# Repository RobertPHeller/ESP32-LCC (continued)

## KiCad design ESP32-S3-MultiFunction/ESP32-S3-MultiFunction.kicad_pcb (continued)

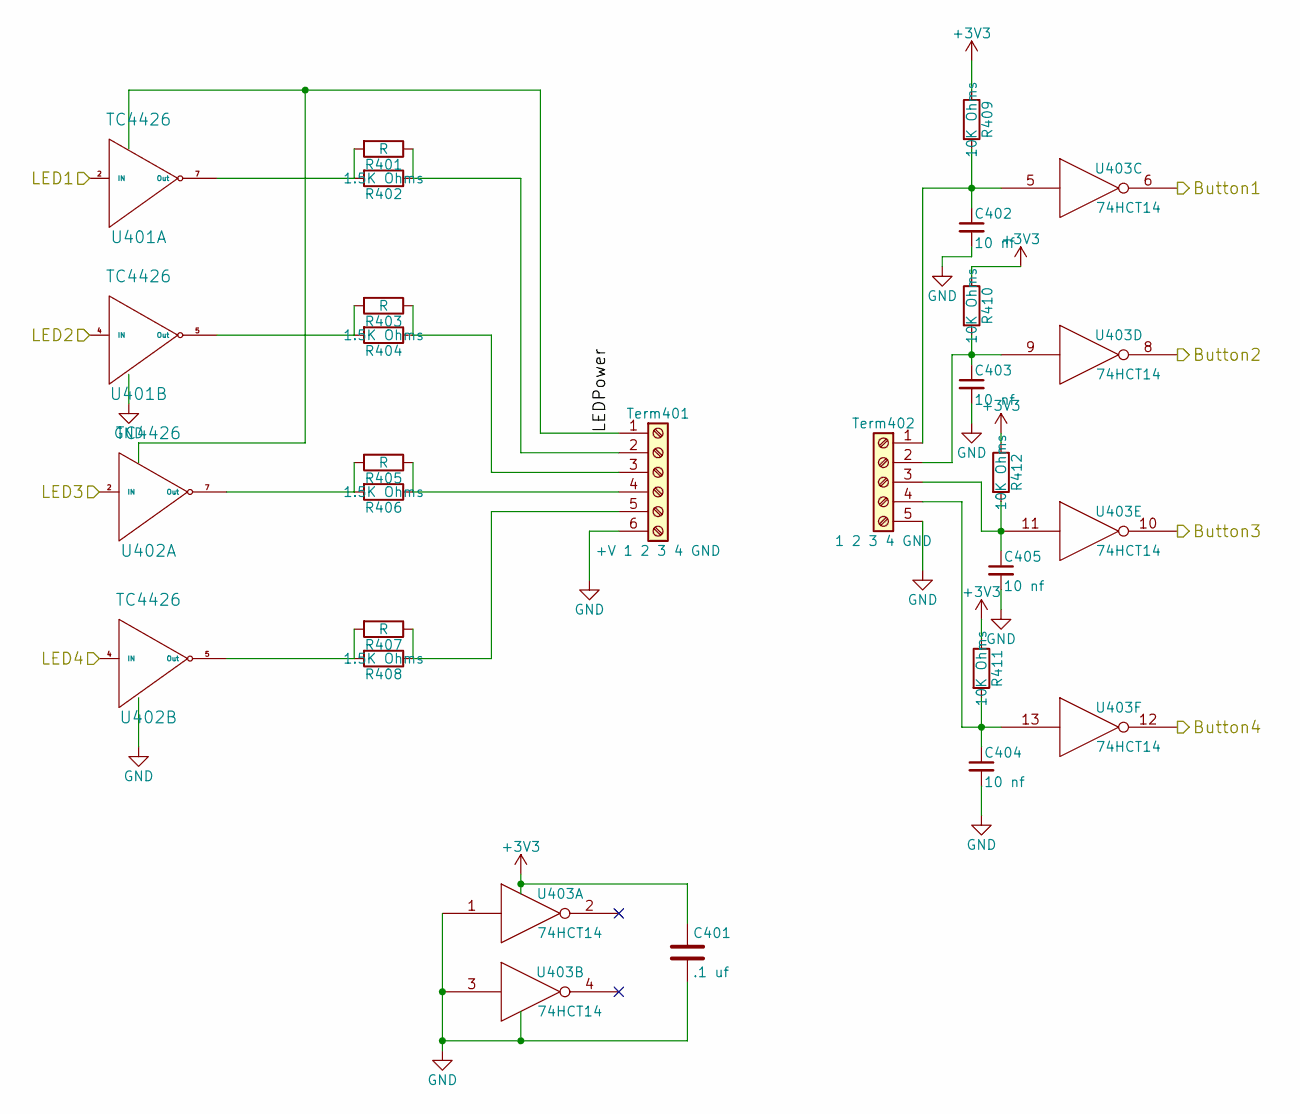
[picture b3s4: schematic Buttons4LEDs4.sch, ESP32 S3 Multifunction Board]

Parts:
C401: .1 uf; C_0603; Mouser Part Number 710-885012206095
C402, C403, C404, C405: 10 nf; C_0603; Mouser Part Number 710-885382206002
R401, R403, R405, R407: R; R_Axial_DIN0207_L6.3mm_D2.5mm_P7.62mm_Horizontal
R402, R404, R406, R408: 1.5K Ohms; R_0603; Mouser Part Number 71-CRCW06031K50JNEAC
R409, R410, R411, R412: 10K Ohms; R_0603; Mouser Part Number 71-CRCW060310K0JNEBC
Term401: +V 1 2 3 4 GND; TerminalBlock_Pheonix_MPT-2.54mm_6pol; Mouser Part Number 651-1725698
Term402: 1 2 3 4 GND; TerminalBlock_Pheonix_MPT-2.54mm_5pol; Mouser Part Number 651-1725685
U401, U402: TC4426; SOIC-8_3.9x4.9mm_Pitch1.27mm; Mouser Part Number 579-TC1426COA713
U403: 74HCT14; SOIC-14_3.9x8.7mm_Pitch1.27mm; Mouser Part Number 595-CD74HC14M

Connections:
/Buttons and LEDs/Button1: U403.6; also elsewhere on the board
/Buttons and LEDs/Button2: U403.8; also elsewhere on the board
/Buttons and LEDs/Button3: U403.10; also elsewhere on the board
/Buttons and LEDs/Button4: U403.12; also elsewhere on the board
/ESP32 MCU/GPIO1(LEDS4): U402.4 (IN); also elsewhere on the board
/ESP32 MCU/GPIO17(LEDS1): U401.2 (IN); also elsewhere on the board
/ESP32 MCU/GPIO18(LEDS2): U401.4 (IN); also elsewhere on the board
/ESP32 MCU/GPIO21(LEDS3): U402.2 (IN); also elsewhere on the board
GND: C401.2, C402.2, C403.2, C404.2, C405.2, Term401.6, Term402.5, U401.3 (GND), U402.3 (GND), U403.1, U403.3, U403.7 (GND); also elsewhere on the board
unnamed: C402.1, R409.2, Term402.1, U403.5
unnamed: C403.1, R410.2, Term402.2, U403.9
unnamed: C404.1, R411.2, Term402.4, U403.13
unnamed: C405.1, R412.2, Term402.3, U403.11
unnamed: R401.1, R402.1, Term401.2
unnamed: R401.2, R402.2, U401.7 (Out)
unnamed: R403.1, R404.1, Term401.3
unnamed: R403.2, R404.2, U401.5 (Out)
unnamed: R405.1, R406.1, Term401.4
unnamed: R405.2, R406.2, U402.7 (Out)
unnamed: R407.1, R408.1, Term401.5
unnamed: R407.2, R408.2, U402.5 (Out)
VPower: Term401.1, U401.6 (VPower), U402.6 (VPower)

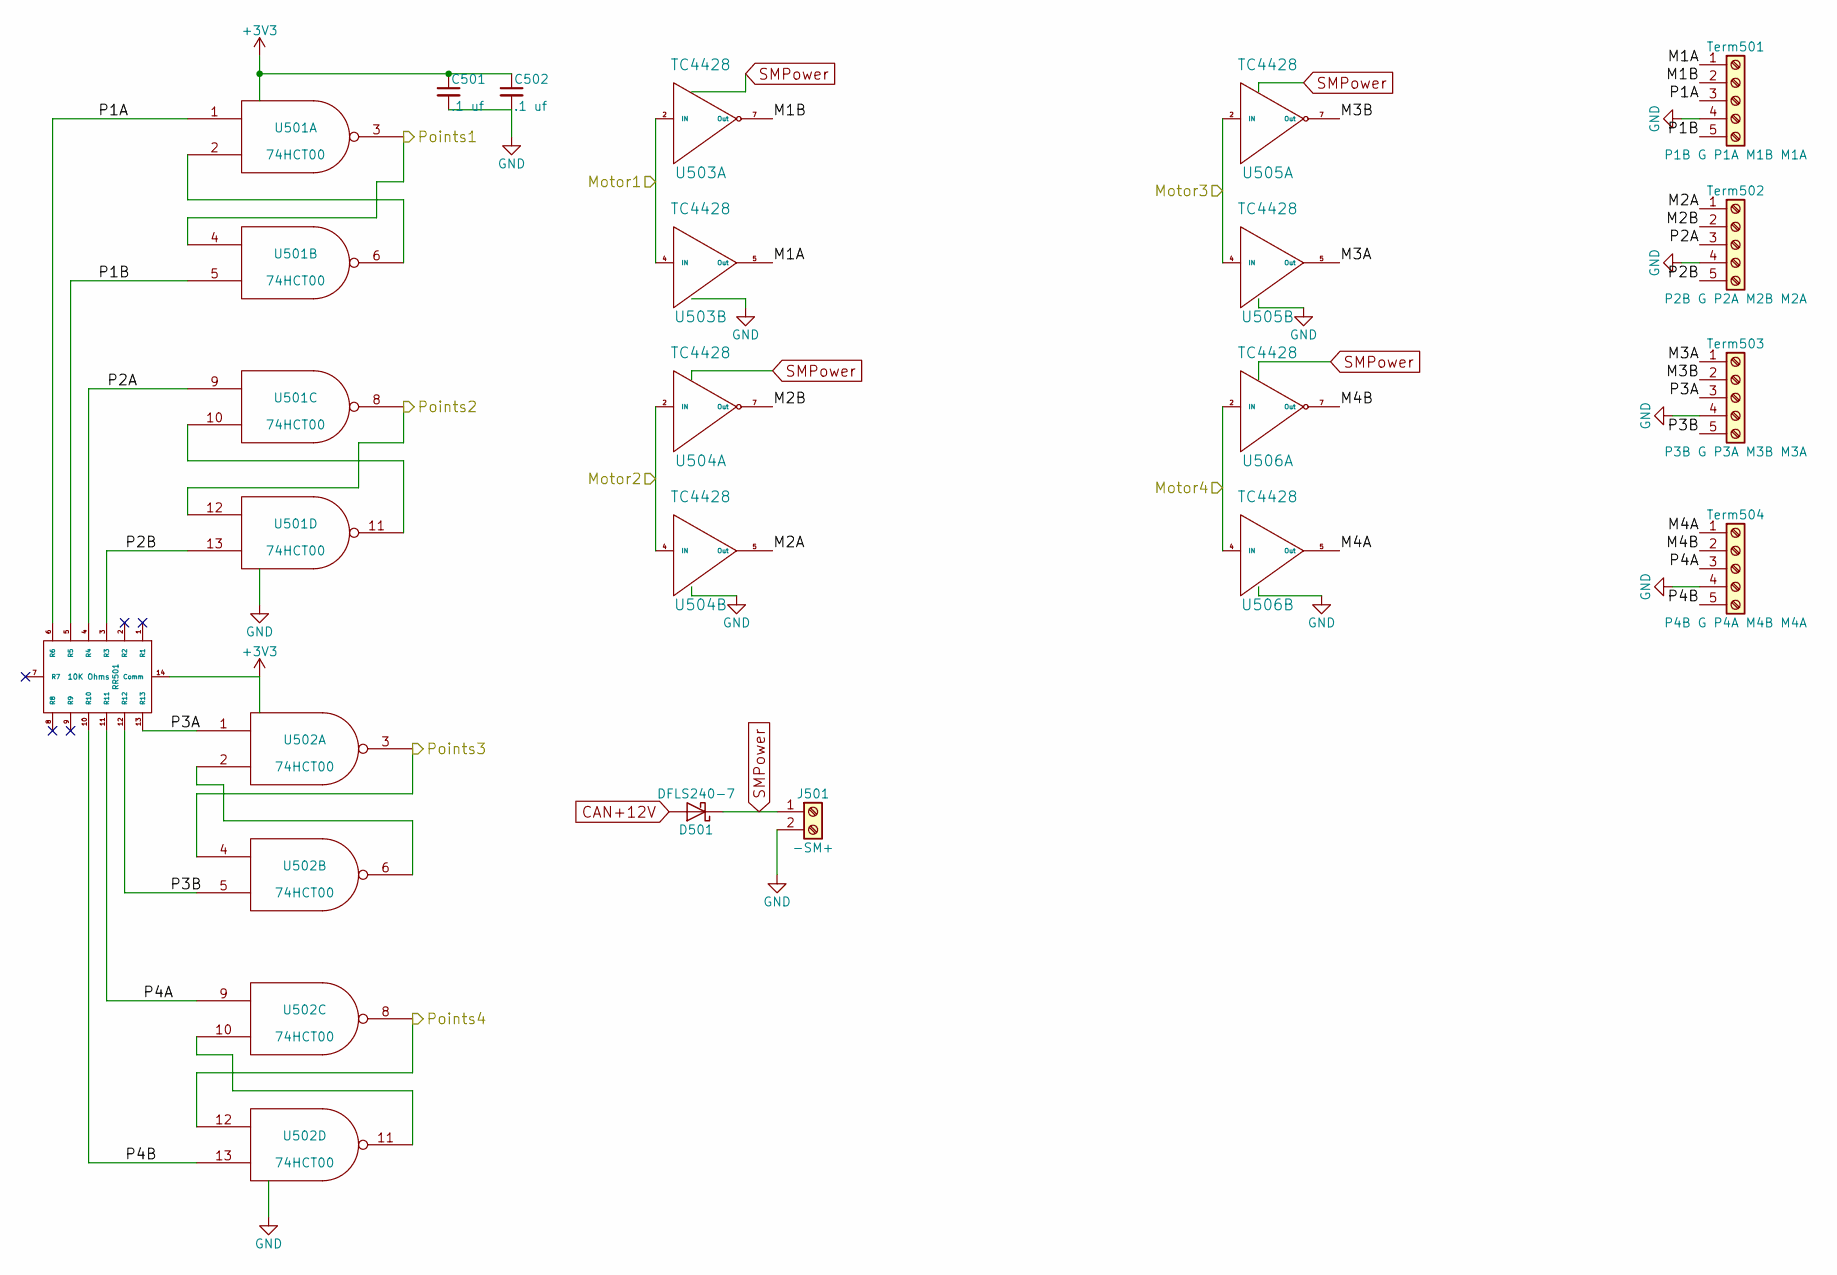
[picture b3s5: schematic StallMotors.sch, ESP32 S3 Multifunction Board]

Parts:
C501, C502: .1 uf; C_0603; Mouser Part Number 710-885012206095
D501: DFLS240-7; D_PowerDI-123; Mouser Part Number 621-DFLS240-7
J501: -SM+; TerminalBlock_Pheonix_MPT-2.54mm_2pol; Mouser Part Number 651-172565
RR501: 10K Ohms; 4814P; Mouser Part Number 652-4814P-2LF-10K
Term501: P1B G P1A M1B M1A; TerminalBlock_Pheonix_MPT-2.54mm_5pol; Mouser Part Number 651-1725685
Term502: P2B G P2A M2B M2A; TerminalBlock_Pheonix_MPT-2.54mm_5pol; Mouser Part Number 651-1725685
Term503: P3B G P3A M3B M3A; TerminalBlock_Pheonix_MPT-2.54mm_5pol; Mouser Part Number 651-1725685
Term504: P4B G P4A M4B M4A; TerminalBlock_Pheonix_MPT-2.54mm_5pol; Mouser Part Number 651-1725685
U501, U502: 74HCT00; SOIC-14_3.9x8.7mm_Pitch1.27mm; Mouser Part Number 595-SN74AHC00D
U503, U504, U505, U506: TC4428; SOIC-8_3.9x4.9mm_Pitch1.27mm; Mouser Part Number 579-TC4428VOA

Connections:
/ESP32 MCU/GPIO8(Motor3): U505.2 (IN), U505.4 (IN); also elsewhere on the board
/ESP32 MCU/GPIO9(Motor1): U503.2 (IN), U503.4 (IN); also elsewhere on the board
/ESP32 MCU/GPIO10(Points4): U502.8, U502.12; also elsewhere on the board
/ESP32 MCU/GPIO11(Motor2): U504.2 (IN), U504.4 (IN); also elsewhere on the board
/ESP32 MCU/GPIO12(Points1): U501.3, U501.4; also elsewhere on the board
/ESP32 MCU/GPIO13(Points2): U501.8, U501.12; also elsewhere on the board
/ESP32 MCU/GPIO14(Points3): U502.3, U502.4; also elsewhere on the board
/ESP32 MCU/GPIO33(Motor4): U506.2 (IN), U506.4 (IN); also elsewhere on the board
/Stall Motors/M1A: Term501.1, U503.5 (Out)
/Stall Motors/M1B: Term501.2, U503.7 (Out)
/Stall Motors/M2A: Term502.1, U504.5 (Out)
/Stall Motors/M2B: Term502.2, U504.7 (Out)
/Stall Motors/M3A: Term503.1, U505.5 (Out)
/Stall Motors/M3B: Term503.2, U505.7 (Out)
/Stall Motors/M4A: Term504.1, U506.5 (Out)
/Stall Motors/M4B: Term504.2, U506.7 (Out)
/Stall Motors/P1A: RR501.6 (R6), Term501.3, U501.1
/Stall Motors/P1B: RR501.5 (R5), Term501.5, U501.5
/Stall Motors/P2A: RR501.4 (R4), Term502.3, U501.9
/Stall Motors/P2B: RR501.3 (R3), Term502.5, U501.13
/Stall Motors/P3A: RR501.13 (R13), Term503.3, U502.1
/Stall Motors/P3B: RR501.12 (R12), Term503.5, U502.5
/Stall Motors/P4A: RR501.11 (R11), Term504.3, U502.9
/Stall Motors/P4B: RR501.10 (R10), Term504.5, U502.13
CAN +12V: D501.2 (A); also elsewhere on the board
GND: C501.2, C502.2, J501.2, Term501.4, Term502.4, Term503.4, Term504.4, U501.7 (GND), U502.7 (GND), U503.3 (GND), U504.3 (GND), U505.3 (GND), U506.3 (GND); also elsewhere on the board
unnamed: U501.2, U501.6
unnamed: U501.10, U501.11
unnamed: U502.2, U502.6
unnamed: U502.10, U502.11
SMPower: D501.1 (K), J501.1, U503.6 (Vdd), U504.6 (Vdd), U505.6 (Vdd), U506.6 (Vdd)

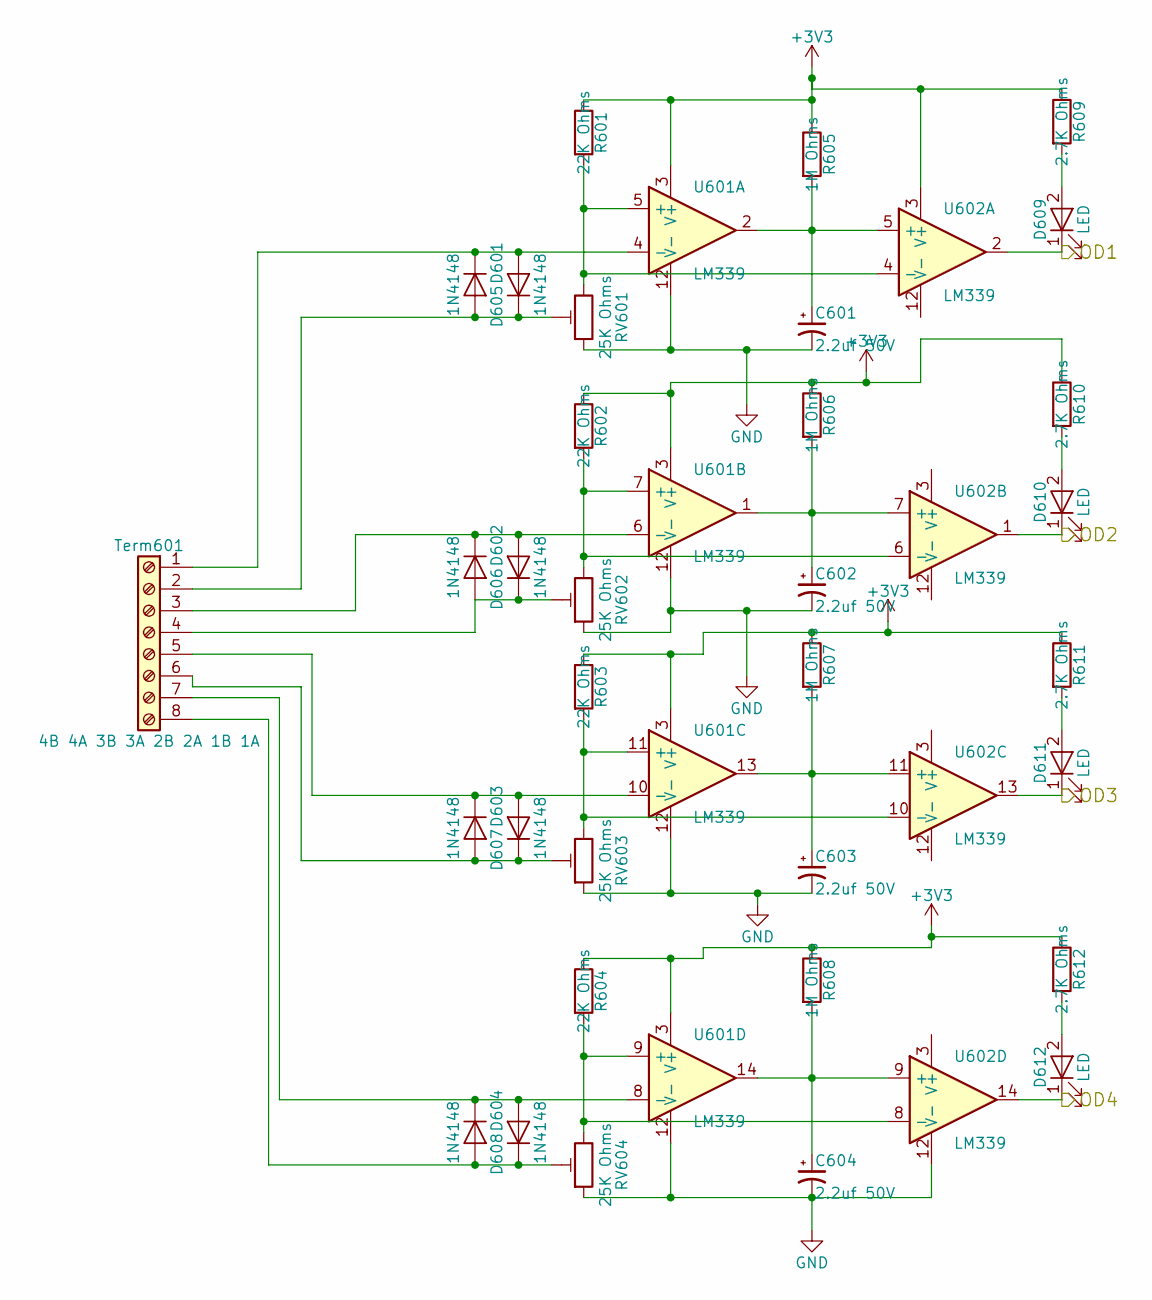
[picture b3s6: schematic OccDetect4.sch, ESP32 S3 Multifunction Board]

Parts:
C601, C602, C603, C604: 2.2uf 50V; CP_Elec_4x5.7; Mouser Part Number 710-865080140002
D601, D602, D603, D604, D605, D606, D607, D608: 1N4148; D_SOD-323; Mouser Part Number 750-1N4148WS-HF
D609, D610, D611, D612: LED; LED_0603; Mouser Part Number 710-150060SS55040
R601, R602, R603, R604: 22K Ohms; R_0603; Mouser Part Number 71-RCG060322K0JNEA
R605, R606, R607, R608: 1M Ohms; R_0603; Mouser Part Number 71-CRCW06031M00JNEAC
R609, R610, R611, R612: 2.7K Ohms; R_0603; Mouser Part Number 71-CRCW06032K70JNEAC
RV601, RV602, RV603, RV604: 25K Ohms; Potentiometer_Trimmer_Bourns_3214J; Mouser Part Number 652-3314J-1-253E
Term601: 4B 4A 3B 3A 2B 2A 1B 1A; TerminalBlock_Pheonix_MPT-2.54mm_8pol; Mouser Part Number 651-1725711
U601, U602: LM339; SOIC-14_3.9x8.7mm_Pitch1.27mm; Mouser Part Number 595-LM339DR

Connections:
/ESP32 MCU/GPIO7(OD4): D612.1 (K), U602.14; also elsewhere on the board
/ESP32 MCU/GPIO34(OD1): D609.1 (K), U602.2; also elsewhere on the board
/ESP32 MCU/GPIO35(OD2): D610.1 (K), U602.1; also elsewhere on the board
/ESP32 MCU/GPIO36(OD3): D611.1 (K), U602.13; also elsewhere on the board
GND: C601.2, C602.2, C603.2, C604.2, RV601.1, RV602.1, RV603.1, RV604.1, U601.12 (V-), U602.12 (V-); also elsewhere on the board
unnamed: C601.1, R605.2, U601.2, U602.5 (+)
unnamed: C602.1, R606.2, U601.1, U602.7 (+)
unnamed: C603.1, R607.2, U601.13, U602.11 (+)
unnamed: C604.1, R608.2, U601.14, U602.9 (+)
unnamed: D601.1 (K), D605.2 (A), Term601.1, U601.4 (-)
unnamed: D601.2 (A), D605.1 (K), RV601.2, Term601.2
unnamed: D602.1 (K), D606.2 (A), Term601.3, U601.6 (-)
unnamed: D602.2 (A), D606.1 (K), RV602.2, Term601.4
unnamed: D603.1 (K), D607.2 (A), Term601.5, U601.10 (-)
unnamed: D603.2 (A), D607.1 (K), RV603.2, Term601.6
unnamed: D604.1 (K), D608.2 (A), Term601.7, U601.8 (-)
unnamed: D604.2 (A), D608.1 (K), RV604.2, Term601.8
unnamed: D609.2 (A), R609.2
unnamed: D610.2 (A), R610.2
unnamed: D611.2 (A), R611.2
unnamed: D612.2 (A), R612.2
unnamed: R601.2, RV601.3, U601.5 (+), U602.4 (-)
unnamed: R602.2, RV602.3, U601.7 (+), U602.6 (-)
unnamed: R603.2, RV603.3, U601.11 (+), U602.10 (-)
unnamed: R604.2, RV604.3, U601.9 (+), U602.8 (-)

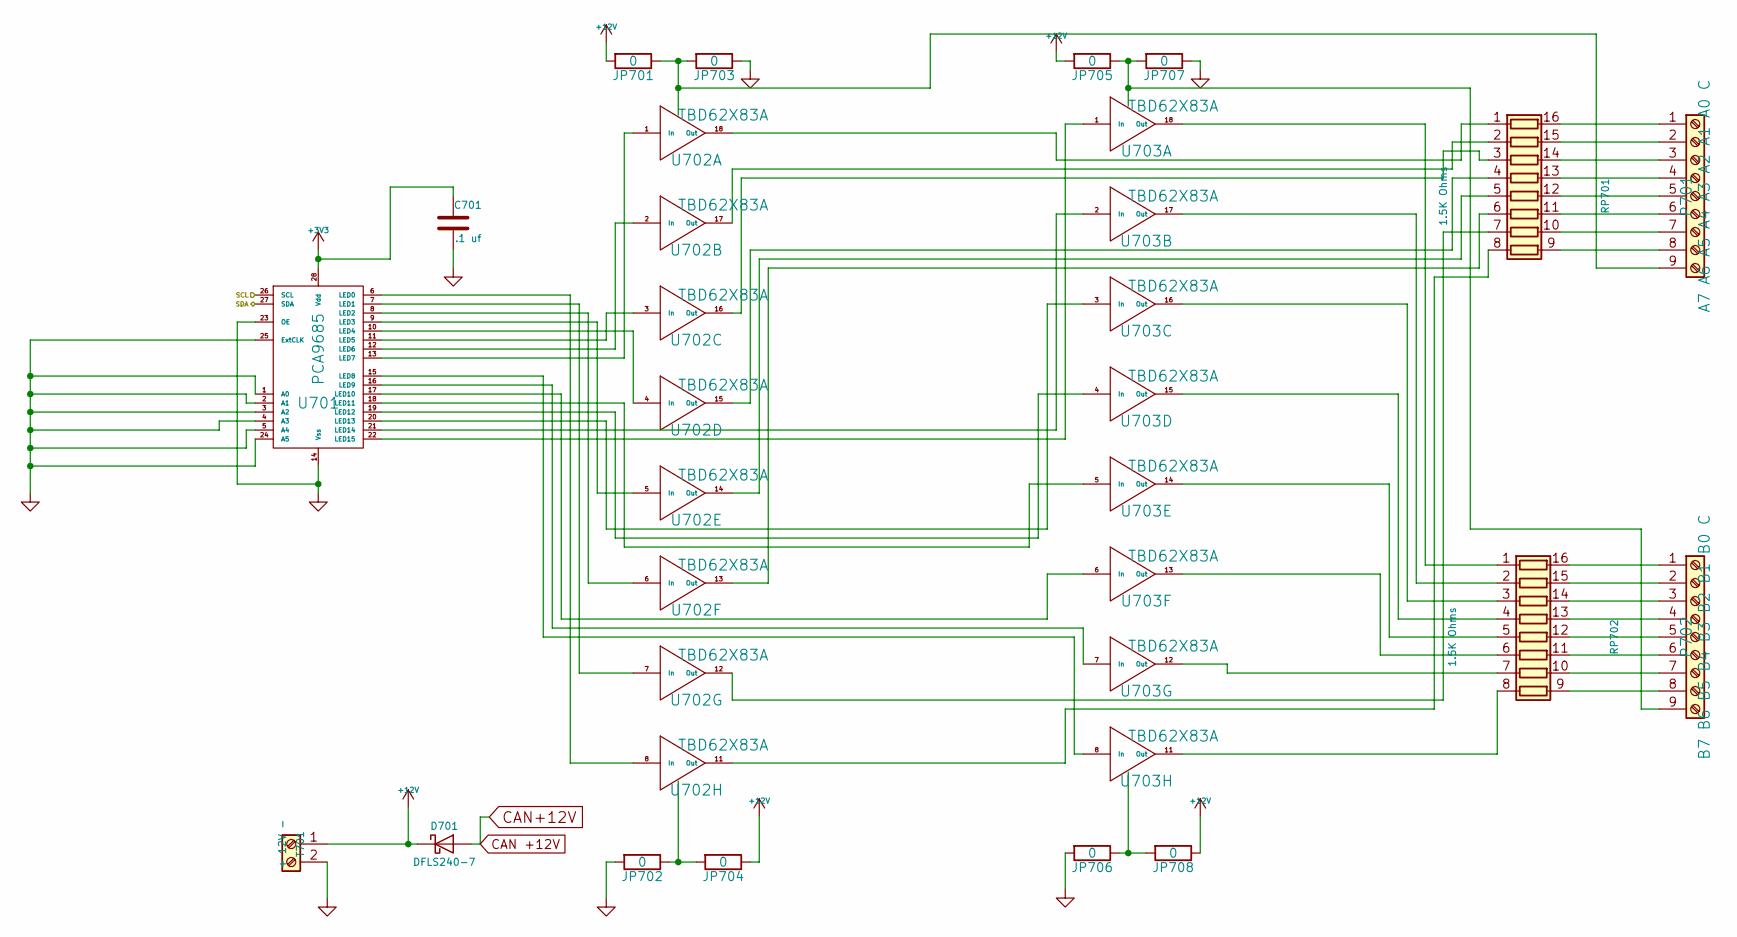
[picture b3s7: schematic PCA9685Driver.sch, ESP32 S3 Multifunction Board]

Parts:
C701: .1 uf; C_0603; Mouser Part Number 710-885012206095
D701: DFLS240-7; D_PowerDI-123; Mouser Part Number 621-DFLS240-7
JP701, JP702, JP703, JP704, JP705, JP706, JP707, JP708: 0; R_1206; Mouser Part Number 71-CRCW12060000Z0EBC
P701: A7 A6 A5 A4 A3 A2 A1 A0 C; TerminalBlock_Pheonix_MPT-2.54mm_9pol; Mouser Part Number 651-1725724
P702: B7 B6 B5 B4 B3 B2 B1 B0 C; TerminalBlock_Pheonix_MPT-2.54mm_9pol; Mouser Part Number 651-1725724
RP701, RP702: 1.5K Ohms; 4816P; Mouser Part Number 652-4816P-T1LF-1.5K
T701: + 12V -; TerminalBlock_Pheonix_MPT-2.54mm_2pol; Mouser Part Number 651-1725656
U701: PCA9685; TSSOP-28_4.4x9.7mm_Pitch0.65mm; Mouser Part Number 771-PCA9685PW,118
U702, U703: TBD62X83A; SOIC-18W_7.5x11.6mm_Pitch1.27mm; Mouser Part Number 757-TBD62083AFG or 757-TBD62783AFG

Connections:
+12V: D701.1 (K), JP701.2, JP704.1, JP705.2, JP708.1, T701.1
/ESP32 MCU/SCL: U701.26 (SCL); also elsewhere on the board
/ESP32 MCU/SDA: U701.27 (SDA); also elsewhere on the board
CAN +12V: D701.2 (A); also elsewhere on the board
GND: C701.2, JP702.2, JP703.1, JP706.2, JP707.1, T701.2, U701.1 (A0), U701.2 (A1), U701.3 (A2), U701.4 (A3), U701.5 (A4), U701.14 (Vss), U701.23 (OE), U701.24 (A5), U701.25 (ExtCLK); also elsewhere on the board
unnamed: JP701.1, JP703.2, P701.9, U702.10 (OC)
unnamed: JP702.1, JP704.2, U702.9 (IC)
unnamed: JP705.1, JP707.2, P702.9, U703.10 (OC)
unnamed: JP706.1, JP708.2, U703.9 (IC)
unnamed: P701.1, RP701.16 (R1.2)
unnamed: P701.2, RP701.15 (R2.2)
unnamed: P701.3, RP701.14 (R3.2)
unnamed: P701.4, RP701.13 (R4.2)
unnamed: P701.5, RP701.12 (R5.2)
unnamed: P701.6, RP701.11 (R6.2)
unnamed: P701.7, RP701.10 (R7.2)
unnamed: P701.8, RP701.9 (R8.2)
unnamed: P702.1, RP702.16 (R1.2)
unnamed: P702.2, RP702.15 (R2.2)
unnamed: P702.3, RP702.14 (R3.2)
unnamed: P702.4, RP702.13 (R4.2)
unnamed: P702.5, RP702.12 (R5.2)
unnamed: P702.6, RP702.11 (R6.2)
unnamed: P702.7, RP702.10 (R7.2)
unnamed: P702.8, RP702.9 (R8.2)
unnamed: RP701.1 (R1.1), U702.18 (Out)
unnamed: RP701.2 (R2.1), U702.17 (Out)
unnamed: RP701.3 (R3.1), U702.16 (Out)
unnamed: RP701.4 (R4.1), U702.15 (Out)
unnamed: RP701.5 (R5.1), U702.14 (Out)
unnamed: RP701.6 (R6.1), U702.13 (Out)
unnamed: RP701.7 (R7.1), U702.12 (Out)
unnamed: RP701.8 (R8.1), U702.11 (Out)
unnamed: RP702.1 (R1.1), U703.18 (Out)
unnamed: RP702.2 (R2.1), U703.17 (Out)
unnamed: RP702.3 (R3.1), U703.16 (Out)
unnamed: RP702.4 (R4.1), U703.15 (Out)
unnamed: RP702.5 (R5.1), U703.14 (Out)
unnamed: RP702.6 (R6.1), U703.13 (Out)
unnamed: RP702.7 (R7.1), U703.12 (Out)
unnamed: RP702.8 (R8.1), U703.11 (Out)
unnamed: U701.6 (LED0), U702.8 (In)
unnamed: U701.7 (LED1), U702.7 (In)
unnamed: U701.8 (LED2), U702.6 (In)
unnamed: U701.9 (LED3), U702.5 (In)
unnamed: U701.10 (LED4), U702.4 (In)
unnamed: U701.11 (LED5), U702.3 (In)
unnamed: U701.12 (LED6), U702.2 (In)
unnamed: U701.13 (LED7), U702.1 (In)
unnamed: U701.15 (LED8), U703.8 (In)
unnamed: U701.16 (LED9), U703.7 (In)
unnamed: U701.17 (LED10), U703.6 (In)
unnamed: U701.18 (LED11), U703.5 (In)
unnamed: U701.19 (LED12), U703.4 (In)
unnamed: U701.20 (LED13), U703.3 (In)
unnamed: U701.21 (LED14), U703.2 (In)
unnamed: U701.22 (LED15), U703.1 (In)

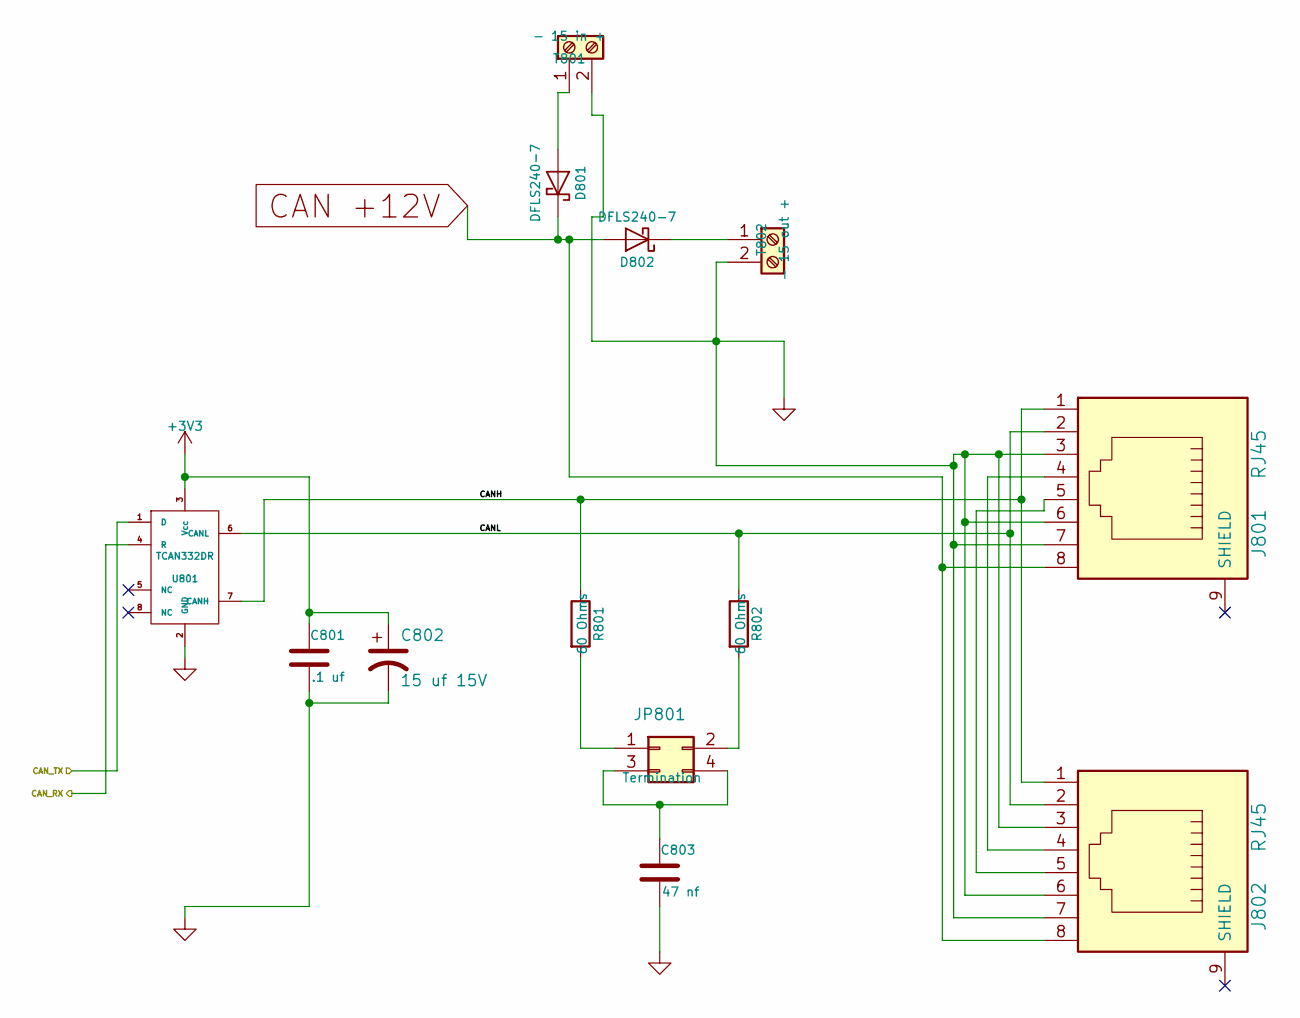
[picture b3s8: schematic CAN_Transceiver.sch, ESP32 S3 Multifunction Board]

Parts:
C801: .1 uf; C_0603; Mouser Part Number 710-885012206095
C802: 15 uf 15V; CP_Elec_4x5.7; Mouser Part Number 647-UUD1C150MCL
C803: 47 nf; C_0603; Mouser Part Number 710-885012206093
D801, D802: DFLS240-7; D_PowerDI-123; Mouser Part Number 621-DFLS240-7
J801, J802: RJ45; RJ45_8N-S; Mouser Part Number 710-615008144221
JP801: Termination; Pin_Header_Straight_2x02_Pitch2.54mm; Mouser Part Number 649-67997-404HLF
R801, R802: 60 Ohms; R_1206; Mouser Part Number 71-CRCW120660R0KNAIF
T801: - 15 in +; TerminalBlock_Pheonix_MPT-2.54mm_2pol; Mouser Part Number 651-1725656
T802: - 15 out +; TerminalBlock_Pheonix_MPT-2.54mm_2pol; Mouser Part Number 651-1725656
U801: TCAN332DR; SOIC-8_3.9x4.9mm_Pitch1.27mm; Mouser Part Number 595-TCAN332DR

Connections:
/CAN Tranceiver/CANH: J801.1, J802.1, R801.1, U801.7 (CANH)
/CAN Tranceiver/CANL: J801.2, J802.2, R802.1, U801.6 (CANL)
/CAN Tranceiver/CAN_RX: U801.4 (R); also elsewhere on the board
/CAN Tranceiver/CAN_TX: U801.1 (D); also elsewhere on the board
CAN +12V: D801.1 (K), D802.2 (A), J801.8, J802.8; also elsewhere on the board
GND: C801.2, C802.2, C803.2, J801.3, J801.6, J801.7, J802.3, J802.6, J802.7, T801.2, T802.2, U801.2 (GND); also elsewhere on the board
unnamed: C803.1, JP801.3, JP801.4
unnamed: D801.2 (A), T801.1
unnamed: D802.1 (K), T802.1
unnamed: J801.4, J802.4
unnamed: J801.5, J802.5
unnamed: JP801.1, R801.2
unnamed: JP801.2, R802.2

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
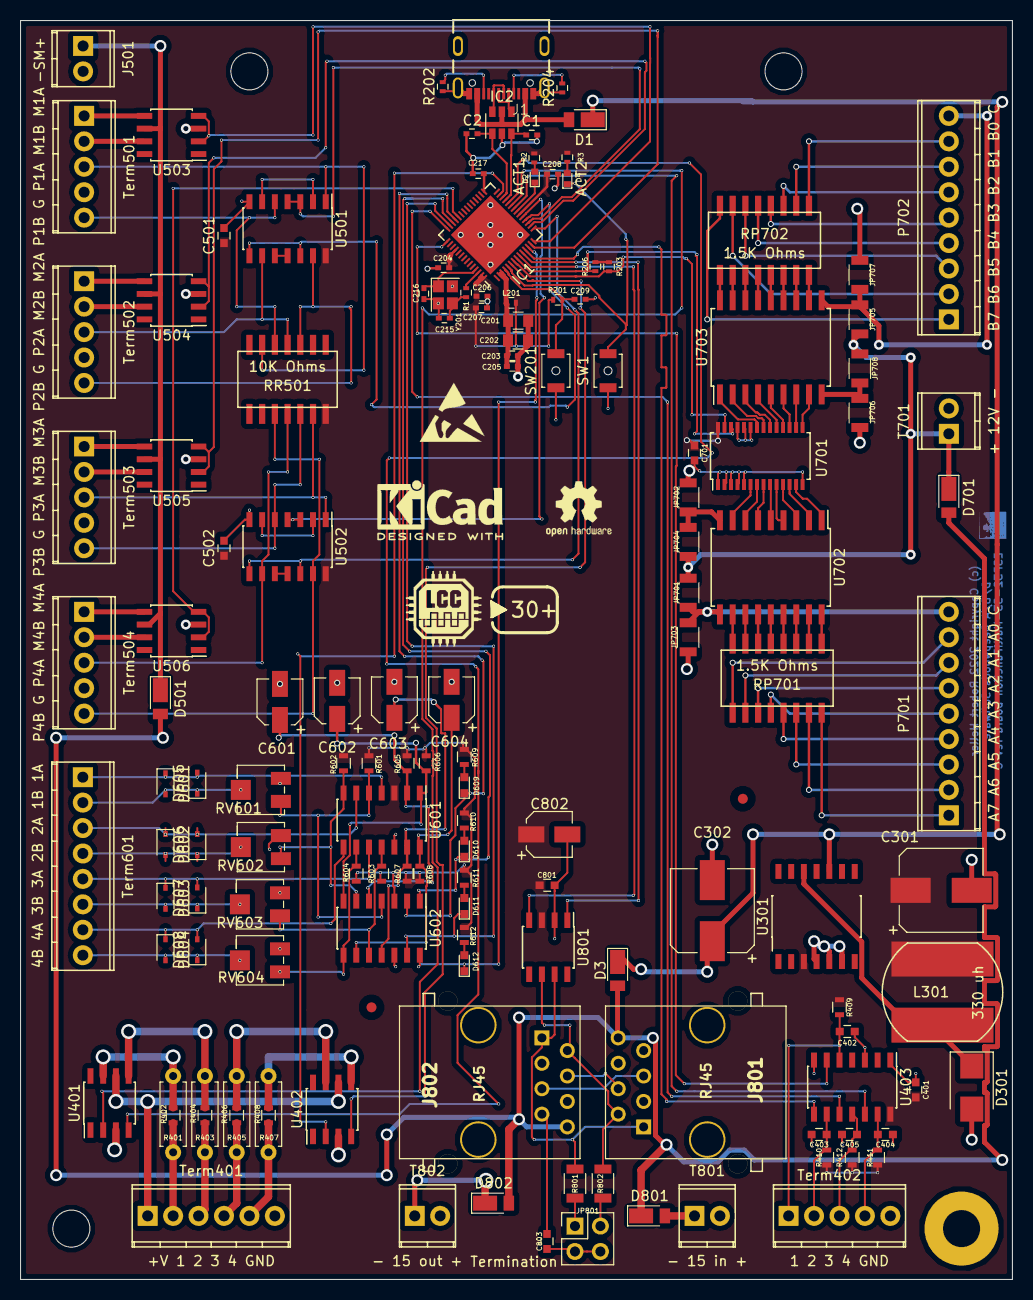
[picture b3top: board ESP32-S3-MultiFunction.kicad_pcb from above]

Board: 2 copper layers, 99.1 x 125.7 mm, 148 parts (1 on the bottom side), 162 nets.

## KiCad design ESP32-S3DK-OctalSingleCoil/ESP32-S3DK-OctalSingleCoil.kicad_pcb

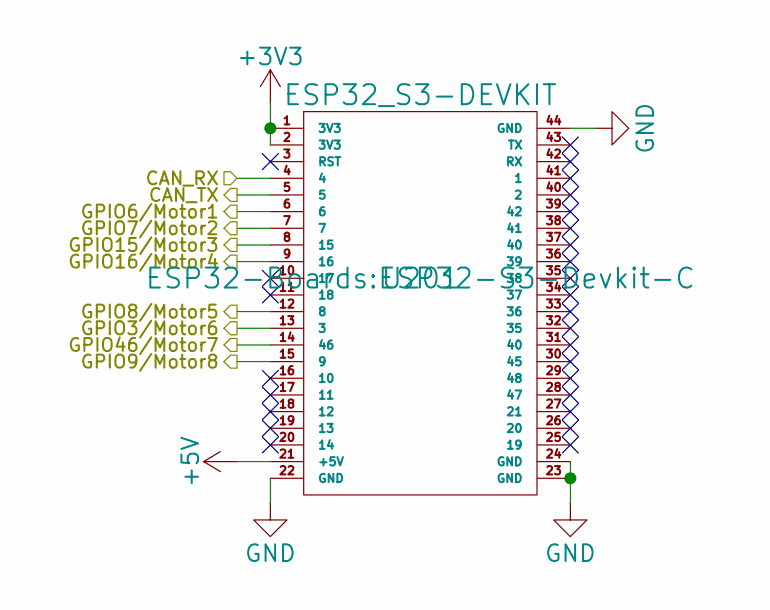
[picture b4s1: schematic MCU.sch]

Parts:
U201: ESP32_S3-DEVKIT; ESP32-S3-Devkit-C

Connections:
+3V3: U201.1 (3V3), U201.2 (3V3); also elsewhere on the board
+5V: U201.21 (+5V); also elsewhere on the board
/CAN Transciver/CAN_RX: U201.4; also elsewhere on the board
/CAN Transciver/CAN_TX: U201.5; also elsewhere on the board
/MCU/GPIO3/Motor6: U201.13 (3); also elsewhere on the board
/MCU/GPIO6/Motor1: U201.6; also elsewhere on the board
/MCU/GPIO7/Motor2: U201.7; also elsewhere on the board
/MCU/GPIO8/Motor5: U201.12 (8); also elsewhere on the board
/MCU/GPIO9/Motor8: U201.15 (9); also elsewhere on the board
/MCU/GPIO15/Motor3: U201.8 (15); also elsewhere on the board
/MCU/GPIO16/Motor4: U201.9 (16); also elsewhere on the board
/MCU/GPIO46/Motor7: U201.14 (46); also elsewhere on the board
GND: U201.22 (GND), U201.23 (GND), U201.24 (GND), U201.44 (GND); also elsewhere on the board

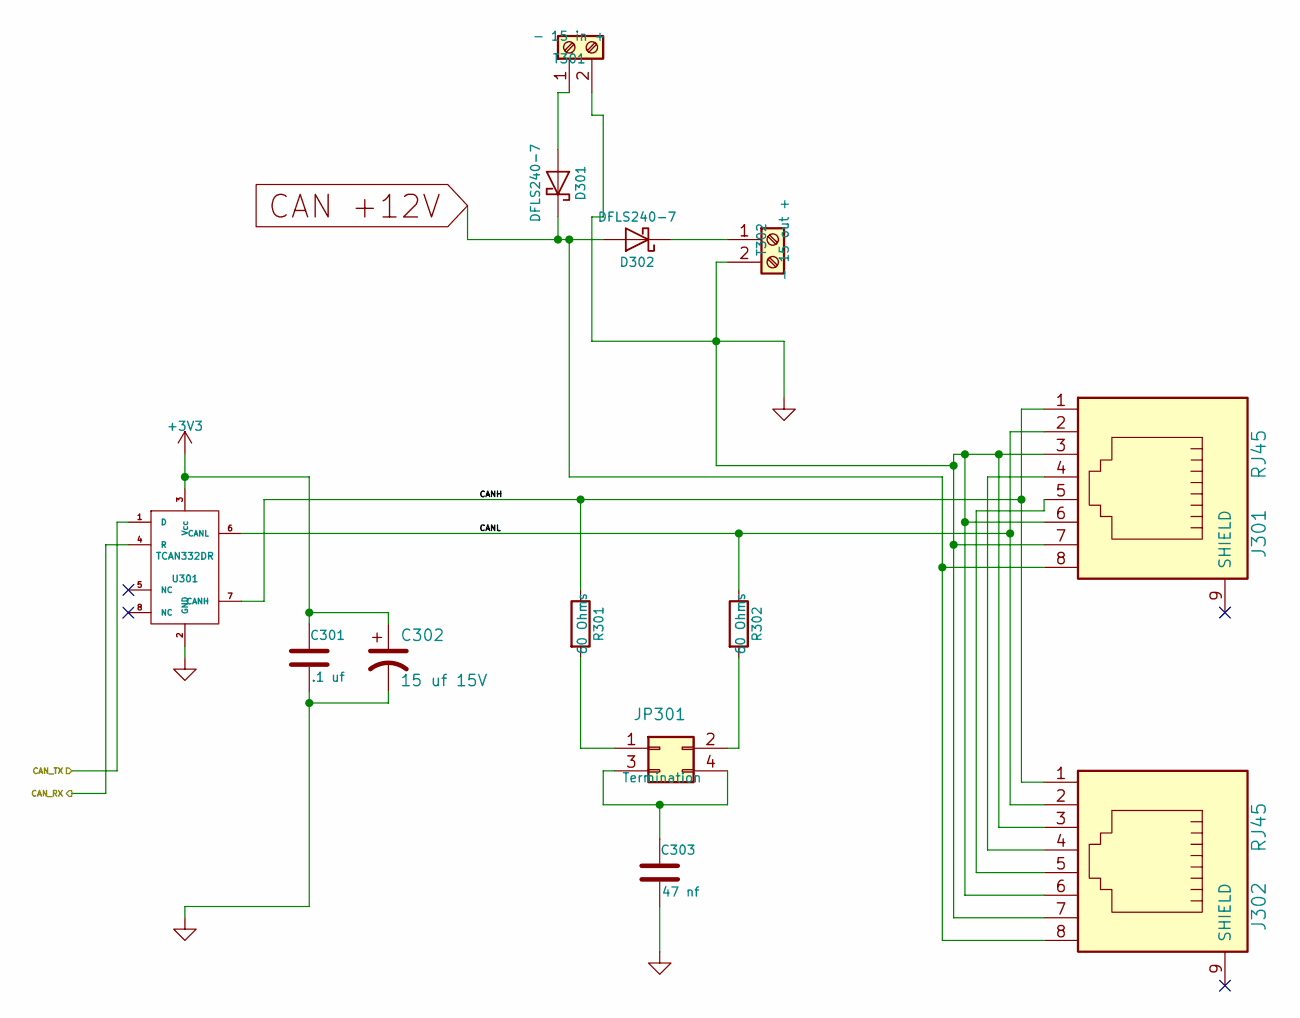
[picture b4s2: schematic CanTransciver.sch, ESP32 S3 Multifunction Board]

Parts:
C301: .1 uf; C_0603; Mouser Part Number 710-885012206095
C302: 15 uf 15V; CP_Elec_4x5.7; Mouser Part Number 647-UUD1C150MCL
C303: 47 nf; C_0603; Mouser Part Number 710-885012206093
D301, D302: DFLS240-7; D_PowerDI-123; Mouser Part Number 621-DFLS240-7
J301, J302: RJ45; RJ45_8N-S; Mouser Part Number 710-615008144221
JP301: Termination; Pin_Header_Straight_2x02_Pitch2.54mm; Mouser Part Number 649-67997-404HLF
R301, R302: 60 Ohms; R_1206; Mouser Part Number 71-CRCW120660R0KNAIF
T301: - 15 in +; TerminalBlock_Pheonix_MPT-2.54mm_2pol; Mouser Part Number 651-1725656
T302: - 15 out +; TerminalBlock_Pheonix_MPT-2.54mm_2pol; Mouser Part Number 651-1725656
U301: TCAN332DR; SOIC-8_3.9x4.9mm_Pitch1.27mm; Mouser Part Number 595-TCAN332DR

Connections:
+3V3: C301.1, C302.1, U301.3 (Vcc); also elsewhere on the board
/CAN Transciver/CANH: J301.1, J302.1, R301.1, U301.7 (CANH)
/CAN Transciver/CANL: J301.2, J302.2, R302.1, U301.6 (CANL)
/CAN Transciver/CAN_RX: U301.4 (R); also elsewhere on the board
/CAN Transciver/CAN_TX: U301.1 (D); also elsewhere on the board
CAN +12V: D301.1 (K), D302.2 (A), J301.8, J302.8; also elsewhere on the board
GND: C301.2, C302.2, C303.2, J301.3, J301.6, J301.7, J302.3, J302.6, J302.7, T301.2, T302.2, U301.2 (GND); also elsewhere on the board
unnamed: C303.1, JP301.3, JP301.4
unnamed: D301.2 (A), T301.1
unnamed: D302.1 (K), T302.1
unnamed: J301.4, J302.4
unnamed: J301.5, J302.5
unnamed: JP301.1, R301.2
unnamed: JP301.2, R302.2

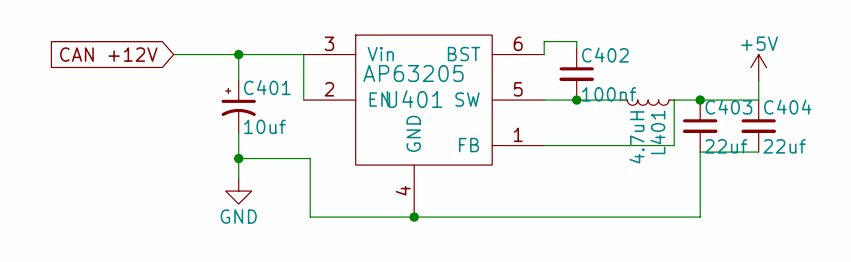
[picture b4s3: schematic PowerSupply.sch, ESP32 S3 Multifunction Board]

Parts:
C401: 10uf; CP_Elec_5x5.3; Mouser Part Number 710-865230542002
C402: 100nf; C_0603; Mouser Part Number 710-885012206020
C403, C404: 22uf; C_0603; Mouser Part Number 603-CC0603MRX6S5B226
L401: 4.7uH; L_7.3x7.3_H4.5; Mouser Part Number 81-B1047AS-4R7NP3
U401: AP63205; TSOT-23-6_MK06A; Mouser Part Number 621-AP63205WU-7

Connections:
+5V: C403.1, C404.1, L401.1, U401.1 (FB); also elsewhere on the board
CAN +12V: C401.1, U401.2 (EN), U401.3 (Vin); also elsewhere on the board
GND: C401.2, C403.2, C404.2, U401.4 (GND); also elsewhere on the board
unnamed: C402.1, U401.6 (BST)
unnamed: C402.2, L401.2, U401.5 (SW)
